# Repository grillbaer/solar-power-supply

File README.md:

# Solar Power Supply - Energy Harvesting

This is a stand-alone solar power supply for operation of micro controller projects with li-ion rechargeable batteries and a highly efficient charge controller. It's optimized to harvest the maximum energy from small solar panels in dull winter weeks, when many MPPT (maximum power point tracking) controllers harvest no energy at all. It's not meant to get the most power out of the panel in bright summer sun. That's where MPPT controllers have their place. For powering a stand-alone application, the supply must work for the worst case.

Charging and power supply of the application work in parallel. When there is more current from the solar panel than needed by the application load, the battery will charge up. When there is less, the battery delivers the missing current.

Be aware that small solar panels only produce a small amount of energy in winter and on dull days. This may be only around a percent of the panel's rated peak performance. So, it's absolutely important to bring down the power consumption of your application to a few milli-amperes. Otherwise it will inevitabely run out of battery after some winter weeks.

You may have a look into my comparison of some ESP32 dev boards and their power consumptions in different sleep modes: https://github.com/grillbaer/esp32-power-consumption-test

IMPORTANT:
* Feel free to use this as a base for own projects. But be aware that you do this at YOUR OWN RISK. I take no responsibility for any caused damages or for the correctness of the information given here!
* Lithium-ion batteries are potentially dangerous. They can cause fire or even explode when treated wrongly! Use only batteries with safety protection circuits! Do not expose them to heat, think about the summer sun! Have a look into the data-sheet for proper handling!

# ThingSpeak Performance Logging

To test and enhance the circuit, I've got an experimental set-up with a 10 Wp 12 V solar panel, two in-parallel Samsung INR18650-35E 3500mAh cells and a ~50 mW load resistor. An ESP32 and two ADS1115 ADCs perform on-going measurement and data transmission to ThingsPeak, see project https://github.com/grillbaer/esp32-iot-logger.

Note that there were several changes in the circuit and set-up over time which influence the results:

https://thingspeak.com/channels/964991

# Shunt Charge Controller V3.3

This charge controller tries to reduce all power losses to the absolute minimum. Almost 100 % of the solar energy goes directly into battery charging and/or the attached load until the battery is fully charged. To prevent over-charging, the N-MOSFET Q1 with a heat sink acts as a shunt that converts excess power into heat when a battery voltage of 4.1 V is reached. The 4.1 V is below the typical maximum allowed battery voltage of 4.20 V to account for component tolerances, battery environment temperature and for the fact that the float charge will not be cut off by this circuit.

The second N-MOSFET Q2 prevents flowback from the battery into the solar panel at night. This could be done by the Schottky diode alone, but the N-MOSFET has only some milli-volts drop during charging whereas the diode would have about 0.3 V.

The controller does not perform any max power-point tracking (MPPT) to get into the peak power production region of the solar panel. The solar panel will work close to the battery voltage. This is not ideal for harvesting the maximum power in the summer, but it is quite well optimized for the low solar irradiance in the middle of winter, where most MPPT trackers do not work at all. This is the goal of the whole project: It does not matter whether we loose some power in the summer, we need to get every milli-watt in the dull winter months!

Notes:
* Hand-select N-MOSFETs with a very low threshold voltage V<sub>GS(th)</sub> of below 2.5 V! Many IRLZ34N have V<sub>GS(th)</sub> up to 4 V which will not work here. Alternatively, select another MOSFET type with guaranteed lower threshold voltage.
* You can leave out R6, R7 and Q2 in the bottom right corner of the schematic and rely on the Schottky diode D1 to prevent flowback from battery. Then, also the op-amp could be a simpler model, since real rail-to-rail for input and output would not be needed. However, the efficiency will drop to about 90 % while charging due to the higher voltage drop of the diode. The other way around, you can leave out the Schottky diode if Q2 is used. This saves about 100 µA leakage current of the diode at night.
* This op-amp type has been chosen because it is a real rail-to-rail type for input and output, works down to below 3 V supply and is really a micro-power one. This is very important, since it always draws its supply current from the battery and it makes a huge difference here whether it needs only 2 µA or 2 mA.
* Also hand-select R1+R2 and R3 to have quite exact values. Otherwise, the upper charging limit voltage may be higher. Lithium-ion batteries must absolutely not be charged with too high voltages, usually not over 4.20 V. Look into the data-sheet of your battery!
* The charging current is not limited by this circuit. Think about the maximum current your solar panel could deliver and use matching batteries. Example: a 10 Wp panel at 3 V has 3.3 A maximum current. So choose (a parallel pair of) batteries which are fine with 3.3 A charging current. In reality, the worst case maximum current of the panel will likely be smaller due to local irradiance, panel temperature and the non-optimum voltage for maximum power. However, keep it on the safe side! Only put identical cells with the same charging state in parallel to avoid high balancing currents!
* Do NOT use batteries in-series by adjusting the max charging voltage of this circuit to 8.2 V. This op-amp is rated for an absolute maximum of 7 V. Also, in-series batteries require load balancing to permanently keep both cells within their safe limits.
* ONLY use lithium-ion batteries with 4.20 V with safety circuit to prevent deep discharge, over-current or short-circuit and also as a second safety against over-charging if this controller gets damaged. Batteries can explode or catch fire!
* The heat sink must be able to lead away the whole maximum power from the solar panel in the warmest expected environment without exceeding the maximum allowed temperature of the FET. This is the drawback of the simple shunt circuit. Do not place the heat-sink in direct sun!

# Circuit Board

The KiCAD files in this project contain a one-sided PCB layout that can be built-up on a 2.54 mm raster breadboard as prototype:

# Prototype

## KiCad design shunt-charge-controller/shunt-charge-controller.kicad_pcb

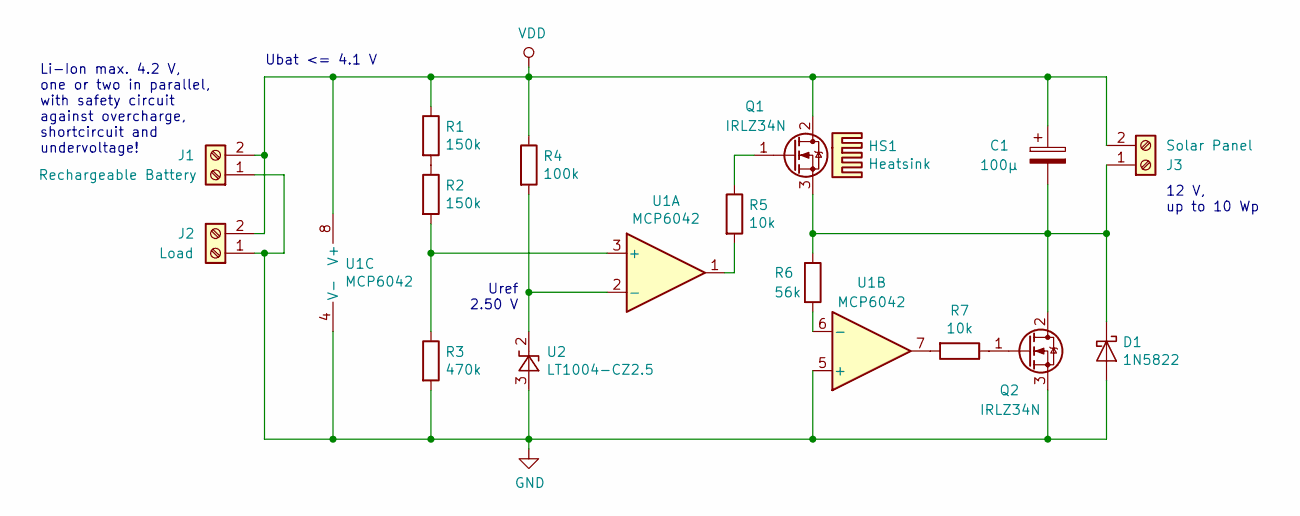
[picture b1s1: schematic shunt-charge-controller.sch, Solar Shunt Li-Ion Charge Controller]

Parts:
C1: 100µ; CP_Radial_D8.0mm_P2.50mm
D1: 1N5822; D_DO-201AD_P15.24mm_Horizontal
HS1: Heatsink
J1: Rechargeable Battery; TerminalBlock_RND_205-00001_1x02_P5.00mm_Horizontal
J2: Load; TerminalBlock_RND_205-00001_1x02_P5.00mm_Horizontal
J3: Solar Panel; TerminalBlock_RND_205-00001_1x02_P5.00mm_Horizontal
Q1, Q2: IRLZ34N; TO-220-3_Vertical
R1, R2: 150k; R_Axial_DIN0207_L6.3mm_D2.5mm_P10.16mm_Horizontal
R3: 470k; R_Axial_DIN0207_L6.3mm_D2.5mm_P10.16mm_Horizontal
R4: 100k; R_Axial_DIN0207_L6.3mm_D2.5mm_P10.16mm_Horizontal
R5, R7: 10k; R_Axial_DIN0207_L6.3mm_D2.5mm_P10.16mm_Horizontal
R6: 56k; R_Axial_DIN0207_L6.3mm_D2.5mm_P10.16mm_Horizontal
U1: MCP6042; DIP-8_W7.62mm
U2: LT1004-CZ2.5; TO-92_Inline

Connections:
GND: D1.2 (A), J1.1, J2.1, Q2.3 (S), R3.2, U1.4 (V-), U1.5 (+), U2.3 (A)
unnamed: C1.2, D1.1 (K), J3.1, Q1.3 (S), Q2.2 (D), R6.1
unnamed: Q1.1 (G), R5.1
unnamed: Q2.1 (G), R7.1
unnamed: R1.2, R2.1
unnamed: R2.2, R3.1, U1.3 (+)
unnamed: R4.2, U1.2 (-), U2.2 (K)
unnamed: R5.2, U1.1
unnamed: R6.2, U1.6 (-)
unnamed: R7.2, U1.7
VDD: C1.1, J1.2, J2.2, J3.2, Q1.2 (D), R1.1, R4.1, U1.8 (V+)

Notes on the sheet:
Uref 2.50 V
12 V, up to 10 Wp
Li-Ion max. 4.2 V, one or two in parallel, with safety circuit against overcharge, shortcircuit and undervoltage!
Ubat <= 4.1 V

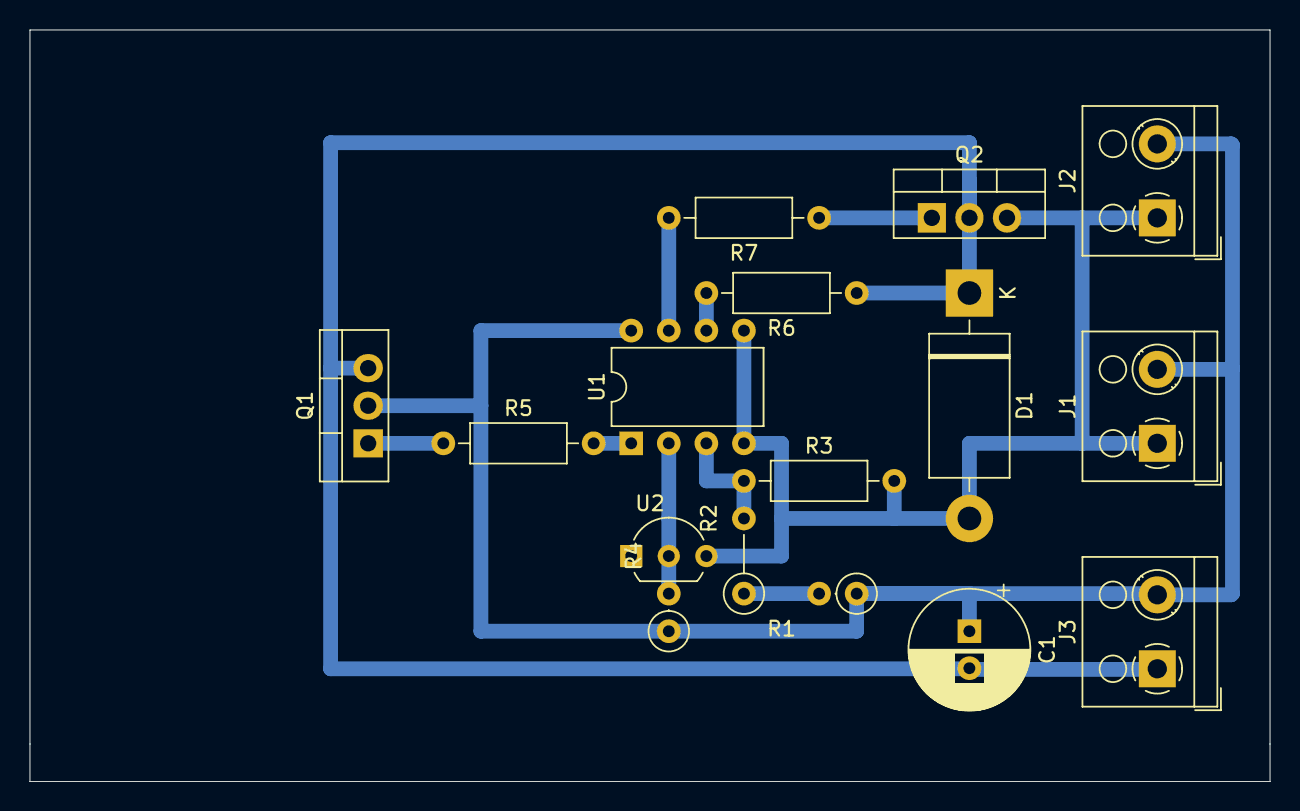
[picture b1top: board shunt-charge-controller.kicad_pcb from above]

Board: 2 copper layers, 83.8 x 50.8 mm, 16 parts (0 on the bottom side), 11 nets.

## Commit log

2020-02-17 schematics V3.1 and V3.3
2020-02-21 PCB layout for breadboard
2020-02-21 added documentation
2020-02-21 fixed typos
2020-02-21 moved kicad files
2020-02-22 updated note on Schottky diode
